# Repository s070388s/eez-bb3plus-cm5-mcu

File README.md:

### This is a WORK IN PROGRESS!

---

### Ownership and License
The contributors are listed in CONTRIB.TXT. 

### Overview

The MCU module uses a high performance STM32 MCU and is pin compatible with Raspberry Pi CM5. The MCU cannot generate an HDMI compatible signal, so a TI TFP410 is used to convert 24-bit RGB to HDMI compatible signal. Since the BB3+ offers dual display: a built-in 5" TFT touchscreen and an external monitor, a 1:2 high speed mux (TS3DV642) is used for destination selection.

### Feature list

* [Raspberry Pi CM5](https://www.raspberrypi.com/products/compute-module-5) form factor (55 x 45 mm)
* [STM32H7R7L8H6H](https://www.st.com/en/microcontrollers-microprocessors/stm32h7r7l8.html) 32-bit High-Performance Arm Cortex-M7 MCU, 600 MHz, NeoChrom GPU
* 32 MB PSRAM
* 32 MB Flash memory
* 4 GB eMMC (100-pin FBGA)
* Two USB ports (1x FS with 1:2 Mux , 1x FS/HS)
* 10/100 Mbps Ethernet
* 24-bit color video output with 1:2 MUX (HDMI® compatible)
* 6-layer PCB (without buried/blind vias)

### Related topics and links

* Intergalaktik [BB3-CM4](https://intergalaktik.eu/projects/bb3-cm4)
* [EEZ BB3+](https://github.com/eez-open/eez-bb3plus)
* [DIB DCP405+](https://github.com/eez-open/dib-dcp405plus) power module
* [EEZ BB3](https://github.com/eez-open/modular-psu)
* [EEZ Studio](https://www.envox.eu/studio/studio-introduction)
* [Discord](https://discord.com/invite/q5KAeeenNG) server
* [X](https://x.com/envox) (ex Twitter)
* [YouTube](https://www.youtube.com/c/eezopen) channel
* [EEVblog forum](https://www.eevblog.com/forum/projects/eez-h25005-a-possible-successor-of-eez-h24005-programmable-power-supply/) discussion

---

This work is financed by [NLnet](https://nlnet.nl/project/BB3-CM5/) foundation

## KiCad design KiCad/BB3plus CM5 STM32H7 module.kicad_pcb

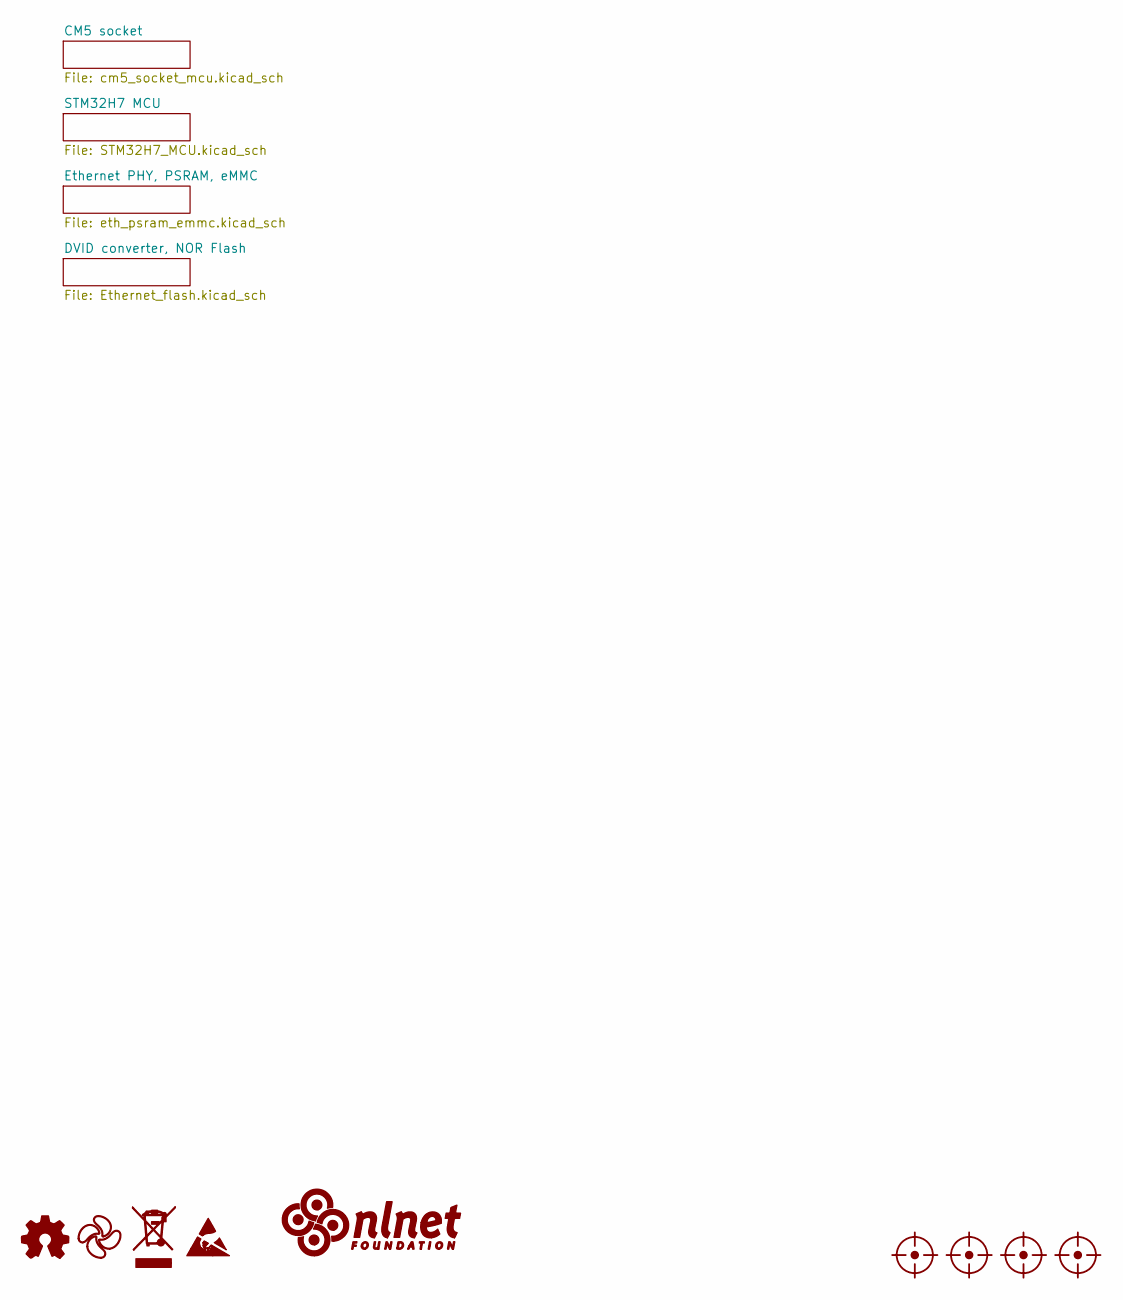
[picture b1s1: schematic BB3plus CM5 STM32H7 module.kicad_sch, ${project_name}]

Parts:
FM1, FM2, FM3, FM4: Fiducial_0.75mm_Mask1.5mm
LOGO1: Open HW logo
LOGO2: EEZ logo; EEZ logo (outline 6mm)
LOGO3: WEEE logo
LOGO4: ESD logo
LOGO5: NLnet logo

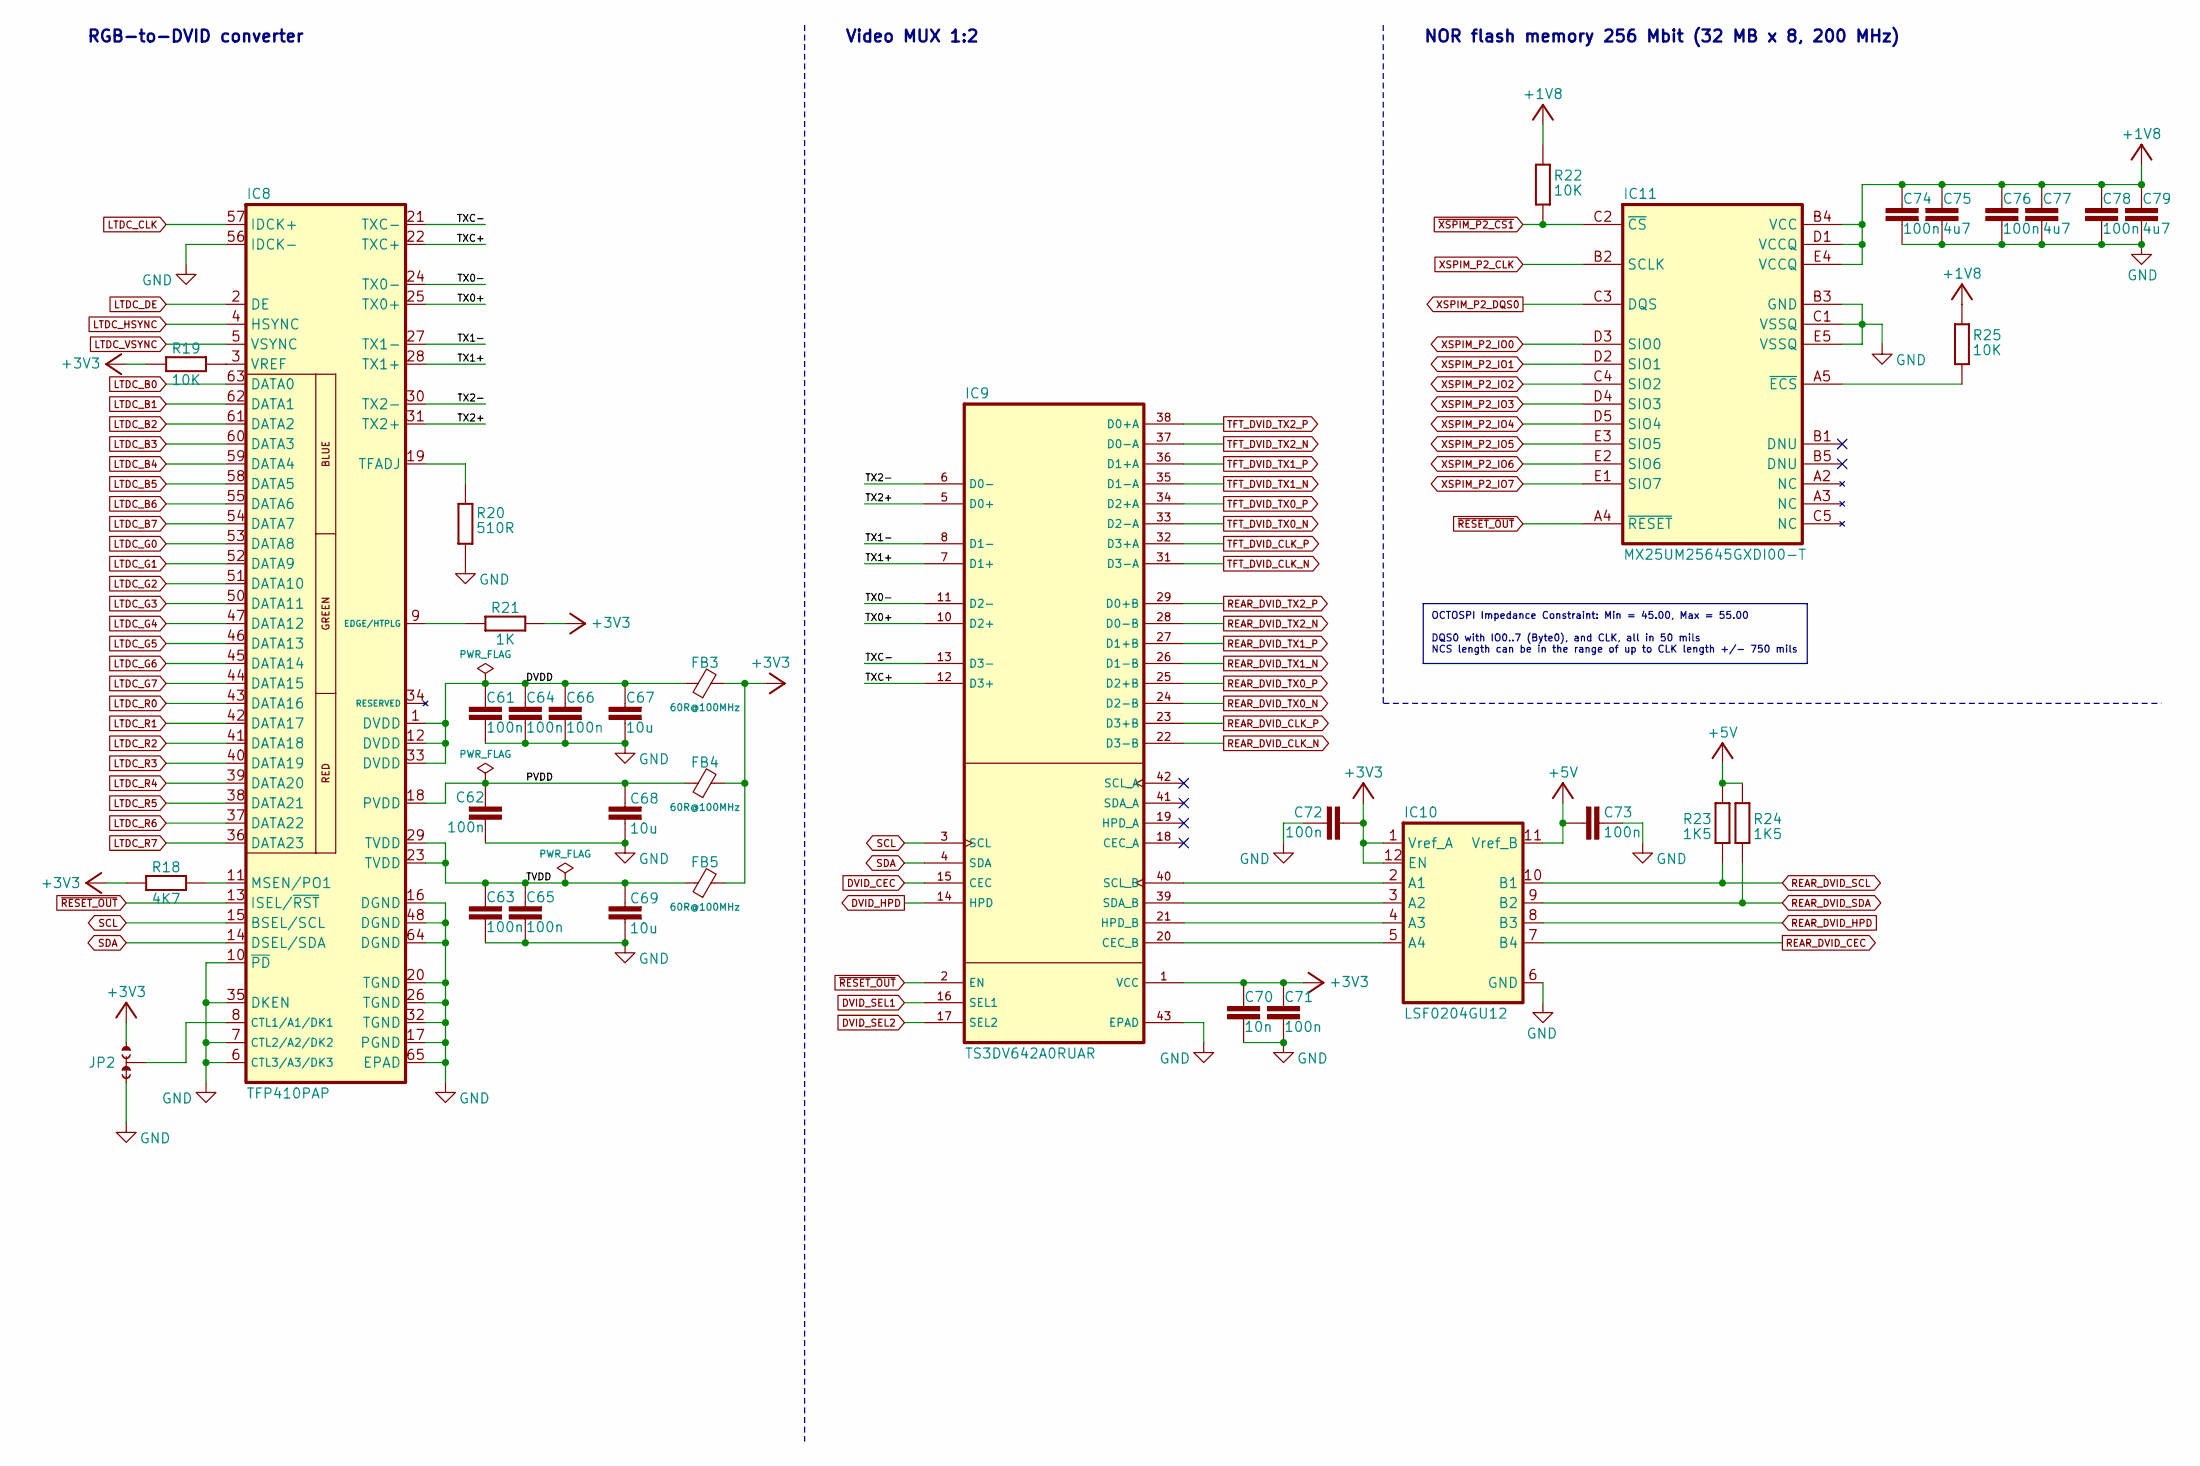
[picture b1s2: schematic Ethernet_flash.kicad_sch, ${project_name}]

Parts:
C61, C62, C63, C64, C65, C66, C71, C72, C73, C74, C76, C78: 100n; C_0402_1005Metric; DigiKey 490-6287-1-ND
C67, C68, C69: 10u; C_0603_1608Metric; DigiKey 1276-1052-6-ND
C70: 10n; C_0402_1005Metric; DigiKey 490-6309-1-ND
C75, C77, C79: 4u7; C_0603_1608Metric; DigiKey 1276-1044-1-ND
FB3, FB4, FB5: 60R@100MHz; BEAD0603; DigiKey 490-7809-1-ND
IC8: TFP410PAP; PAP64_5X5-L; DigiKey 296-12666-ND
IC9: TS3DV642A0RUAR; RUA42_7P55X2P05; DigiKey 296-39510-1-ND
IC10: LSF0204GU12; XQFN12_SOT1174-1_NEX-L; DigiKey 1727-LSF0102DCHCT-ND
IC11: MX25UM25645GXDI00-T; APS256XXN-OBR-BG_APY-L; DigiKey 1092-MX25UM25645GXDI00-ND
JP2: JP3 shorted (0603)
R18: 4K7; R_0402_1005Metric; DigiKey 13-RC0402FR-104K7LCT-ND
R19, R22, R25: 10K; R_0402_1005Metric; DigiKey 311-10.0KLRCT-ND
R20: 510R; R_0402_1005Metric; DigiKey 13-RC0402FR-13510RLCT-ND
R21: 1K; R_0402_1005Metric; DigiKey 13-RC0402FR-131KLCT-ND
R23, R24: 1K5; R_0402_1005Metric; DigiKey 311-1.50KLRCT-ND

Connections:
+1V8: C74.1, C75.1, C76.1, C77.1, C78.1, C79.1, IC11.B4 (VCC), IC11.D1 (VCCQ), IC11.E4 (VCCQ), R22.2, R25.2; also elsewhere on the board
+3V3: C70.1, C71.1, C72.2, FB3.2, FB4.2, FB5.2, IC9.1 (VCC), IC10.1 (Vref_A), IC10.12 (EN), JP2.NO, R18.1, R19.2, R21.2; also elsewhere on the board
+5V: C73.2, IC10.11 (Vref_B), R23.2, R24.2; also elsewhere on the board
/DVID converter, NOR Flash/DVDD: C61.1, C64.1, C66.1, C67.1, FB3.1, IC8.1 (DVDD), IC8.12 (DVDD), IC8.33 (DVDD)
/DVID converter, NOR Flash/PVDD: C62.1, C68.2, FB4.1, IC8.18 (PVDD)
/DVID converter, NOR Flash/TVDD: C63.1, C65.1, C69.2, FB5.1, IC8.23 (TVDD), IC8.29 (TVDD)
/DVID converter, NOR Flash/TX0+: IC8.25 (TX0+), IC9.10 (D2+)
/DVID converter, NOR Flash/TX0-: IC8.24 (TX0-), IC9.11 (D2-)
/DVID converter, NOR Flash/TX1+: IC8.28 (TX1+), IC9.7 (D1+)
/DVID converter, NOR Flash/TX1-: IC8.27 (TX1-), IC9.8 (D1-)
/DVID converter, NOR Flash/TX2+: IC8.31 (TX2+), IC9.5 (D0+)
/DVID converter, NOR Flash/TX2-: IC8.30 (TX2-), IC9.6 (D0-)
/DVID converter, NOR Flash/TXC+: IC8.22 (TXC+), IC9.12 (D3+)
/DVID converter, NOR Flash/TXC-: IC8.21 (TXC-), IC9.13 (D3-)
DVID_CEC: IC9.15 (CEC); also elsewhere on the board
DVID_HPD: IC9.14 (HPD); also elsewhere on the board
DVID_SEL1: IC9.16 (SEL1); also elsewhere on the board
DVID_SEL2: IC9.17 (SEL2); also elsewhere on the board
GND: C61.2, C62.2, C63.2, C64.2, C65.2, C66.2, C67.2, C68.1, C69.1, C70.2, C71.2, C72.1, C73.1, C74.2, C75.2, C76.2, C77.2, C78.2, C79.2, IC8.6 (CTL3/A3/DK3), IC8.7 (CTL2/A2/DK2), IC8.10 (~PD), IC8.16 (DGND), IC8.17 (PGND), IC8.20 (TGND), IC8.26 (TGND), IC8.32 (TGND), IC8.35 (DKEN), IC8.48 (DGND), IC8.56 (IDCK-), IC8.64 (DGND), IC8.65 (EPAD), IC9.43 (EPAD), IC10.6 (GND), IC11.B3 (GND), IC11.C1 (VSSQ), IC11.E5 (VSSQ), JP2.NC, R20.2; also elsewhere on the board
LTDC_B0: IC8.63 (DATA0); also elsewhere on the board
LTDC_B1: IC8.62 (DATA1); also elsewhere on the board
LTDC_B2: IC8.61 (DATA2); also elsewhere on the board
LTDC_B3: IC8.60 (DATA3); also elsewhere on the board
LTDC_B4: IC8.59 (DATA4); also elsewhere on the board
LTDC_B5: IC8.58 (DATA5); also elsewhere on the board
LTDC_B6: IC8.55 (DATA6); also elsewhere on the board
LTDC_B7: IC8.54 (DATA7); also elsewhere on the board
LTDC_CLK: IC8.57 (IDCK+); also elsewhere on the board
LTDC_DE: IC8.2 (DE); also elsewhere on the board
LTDC_G0: IC8.53 (DATA8); also elsewhere on the board
LTDC_G1: IC8.52 (DATA9); also elsewhere on the board
LTDC_G2: IC8.51 (DATA10); also elsewhere on the board
LTDC_G3: IC8.50 (DATA11); also elsewhere on the board
LTDC_G4: IC8.47 (DATA12); also elsewhere on the board
LTDC_G5: IC8.46 (DATA13); also elsewhere on the board
LTDC_G6: IC8.45 (DATA14); also elsewhere on the board
LTDC_G7: IC8.44 (DATA15); also elsewhere on the board
LTDC_HSYNC: IC8.4 (HSYNC); also elsewhere on the board
LTDC_R0: IC8.43 (DATA16); also elsewhere on the board
LTDC_R1: IC8.42 (DATA17); also elsewhere on the board
LTDC_R2: IC8.41 (DATA18); also elsewhere on the board
LTDC_R3: IC8.40 (DATA19); also elsewhere on the board
LTDC_R4: IC8.39 (DATA20); also elsewhere on the board
LTDC_R5: IC8.38 (DATA21); also elsewhere on the board
LTDC_R6: IC8.37 (DATA22); also elsewhere on the board
LTDC_R7: IC8.36 (DATA23); also elsewhere on the board
LTDC_VSYNC: IC8.5 (VSYNC); also elsewhere on the board
unnamed: IC8.8 (CTL1/A1/DK1), JP2.COM
unnamed: IC8.9 (EDGE/HTPLG), R21.1
unnamed: IC8.11 (MSEN/PO1), R18.2
unnamed: IC8.19 (TFADJ), R20.1
unnamed: IC8.3 (VREF), R19.1
unnamed: IC9.40 (SCL_B), IC10.2 (A1)
unnamed: IC9.39 (SDA_B), IC10.3 (A2)
unnamed: IC9.21 (HPD_B), IC10.4 (A3)
unnamed: IC9.20 (CEC_B), IC10.5 (A4)
unnamed: IC11.A5 (~ECS), R25.1
REAR_DVID_CEC: IC10.7 (B4); also elsewhere on the board
REAR_DVID_CLK_N: IC9.22 (D3-B); also elsewhere on the board
REAR_DVID_CLK_P: IC9.23 (D3+B); also elsewhere on the board
REAR_DVID_HPD: IC10.8 (B3); also elsewhere on the board
REAR_DVID_SCL: IC10.10 (B1), R23.1; also elsewhere on the board
REAR_DVID_SDA: IC10.9 (B2), R24.1; also elsewhere on the board
REAR_DVID_TX0_N: IC9.24 (D2-B); also elsewhere on the board
REAR_DVID_TX0_P: IC9.25 (D2+B); also elsewhere on the board
REAR_DVID_TX1_N: IC9.26 (D1-B); also elsewhere on the board
REAR_DVID_TX1_P: IC9.27 (D1+B); also elsewhere on the board
REAR_DVID_TX2_N: IC9.28 (D0-B); also elsewhere on the board
REAR_DVID_TX2_P: IC9.29 (D0+B); also elsewhere on the board
SCL: IC8.15 (BSEL/SCL), IC9.3 (SCL); also elsewhere on the board
SDA: IC8.14 (DSEL/SDA), IC9.4 (SDA); also elsewhere on the board
TFT_DVID_CLK_N: IC9.31 (D3-A); also elsewhere on the board
TFT_DVID_CLK_P: IC9.32 (D3+A); also elsewhere on the board
TFT_DVID_TX0_N: IC9.33 (D2-A); also elsewhere on the board
TFT_DVID_TX0_P: IC9.34 (D2+A); also elsewhere on the board
TFT_DVID_TX1_N: IC9.35 (D1-A); also elsewhere on the board
TFT_DVID_TX1_P: IC9.36 (D1+A); also elsewhere on the board
TFT_DVID_TX2_N: IC9.37 (D0-A); also elsewhere on the board
TFT_DVID_TX2_P: IC9.38 (D0+A); also elsewhere on the board
XSPIM_P2_CLK: IC11.B2 (SCLK); also elsewhere on the board
XSPIM_P2_DQS0: IC11.C3 (DQS); also elsewhere on the board
XSPIM_P2_IO0: IC11.D3 (SIO0); also elsewhere on the board
XSPIM_P2_IO1: IC11.D2 (SIO1); also elsewhere on the board
XSPIM_P2_IO2: IC11.C4 (SIO2); also elsewhere on the board
XSPIM_P2_IO3: IC11.D4 (SIO3); also elsewhere on the board
XSPIM_P2_IO4: IC11.D5 (SIO4); also elsewhere on the board
XSPIM_P2_IO5: IC11.E3 (SIO5); also elsewhere on the board
XSPIM_P2_IO6: IC11.E2 (SIO6); also elsewhere on the board
XSPIM_P2_IO7: IC11.E1 (SIO7); also elsewhere on the board
~RESET_OUT: IC8.13 (ISEL/~RST), IC9.2 (EN), IC11.A4 (~RESET); also elsewhere on the board
~XSPIM_P2_CS1: IC11.C2 (~CS), R22.1; also elsewhere on the board

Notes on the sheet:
RGB-to-DVID converter
Video MUX 1:2
NOR flash memory 256 Mbit (32 MB x 8, 200 MHz)
OCTOSPI Impedance Constraint: Min = 45.00, Max = 55.00 DQS0 with IO0..7 (Byte0), and CLK, all in 50 mils NCS length can be in the range of up to CLK length +/- 750 mils

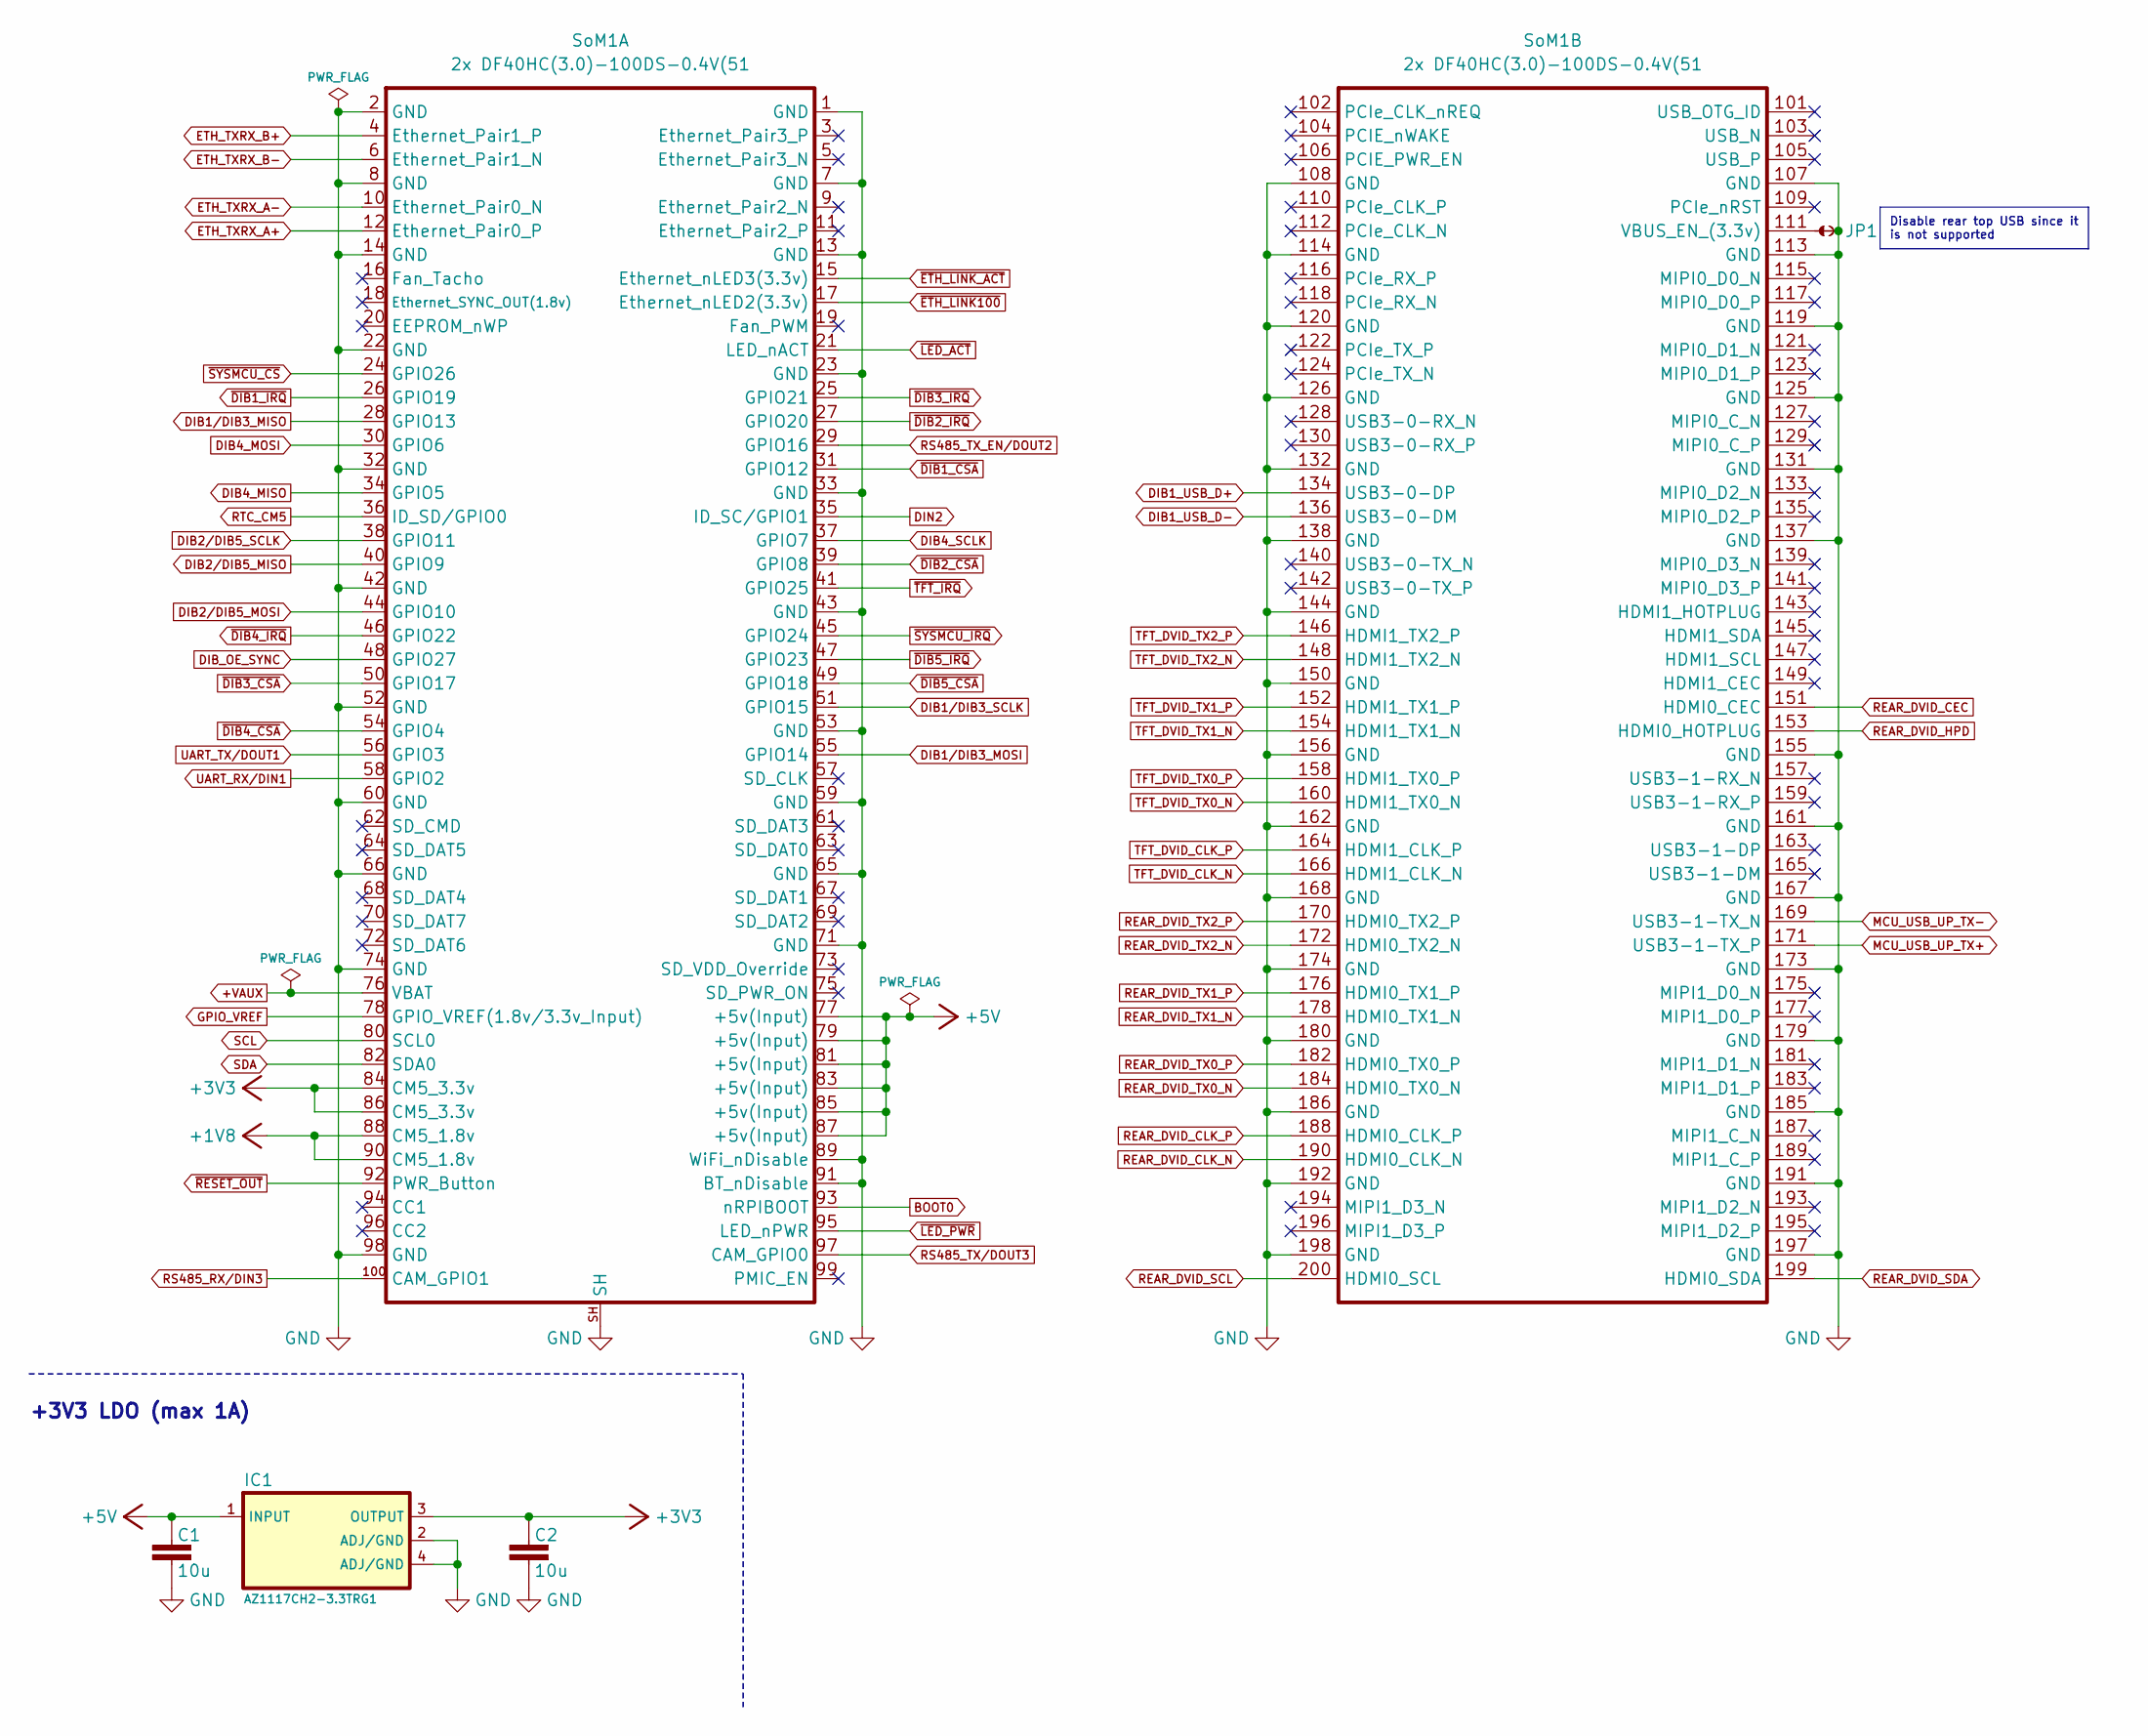
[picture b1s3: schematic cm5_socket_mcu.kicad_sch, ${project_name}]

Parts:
C1, C2: 10u; C_0603_1608Metric; DigiKey 1276-1052-6-ND
IC1: AZ1117CH2-3.3TRG1; SOT223; DigiKey 31-AZ1117CH2-3.3TRG1CT-ND
JP1: JP2 shorted (0603)
SoM1: 2x DF40HC(3.0)-100DS-0.4V(51; Raspberry-Pi-CM5 (SoM); DigiKey H11614CT-ND

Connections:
+1V8: SoM1.88 (CM5_1.8v), SoM1.90 (CM5_1.8v); also elsewhere on the board
+3V3: C2.2, IC1.3 (OUTPUT), SoM1.84 (CM5_3.3v), SoM1.86 (CM5_3.3v); also elsewhere on the board
+5V: C1.2, IC1.1 (INPUT), SoM1.77 (+5v(Input)), SoM1.79 (+5v(Input)), SoM1.81 (+5v(Input)), SoM1.83 (+5v(Input)), SoM1.85 (+5v(Input)), SoM1.87 (+5v(Input)); also elsewhere on the board
+VAUX: SoM1.76 (VBAT); also elsewhere on the board
BOOT0: SoM1.93 (nRPIBOOT); also elsewhere on the board
DIB1_USB_D+: SoM1.134 (USB3-0-DP); also elsewhere on the board
DIB1_USB_D-: SoM1.136 (USB3-0-DM); also elsewhere on the board
DIB1/DIB3_MISO: SoM1.28 (GPIO13); also elsewhere on the board
DIB1/DIB3_MOSI: SoM1.55 (GPIO14); also elsewhere on the board
DIB1/DIB3_SCLK: SoM1.51 (GPIO15); also elsewhere on the board
DIB2/DIB5_MISO: SoM1.40 (GPIO9); also elsewhere on the board
DIB2/DIB5_MOSI: SoM1.44 (GPIO10); also elsewhere on the board
DIB2/DIB5_SCLK: SoM1.38 (GPIO11); also elsewhere on the board
DIB4_MISO: SoM1.34 (GPIO5); also elsewhere on the board
DIB4_MOSI: SoM1.30 (GPIO6); also elsewhere on the board
DIB4_SCLK: SoM1.37 (GPIO7); also elsewhere on the board
DIB_OE_SYNC: SoM1.48 (GPIO27); also elsewhere on the board
DIN2: SoM1.35 (ID_SC/GPIO1); also elsewhere on the board
ETH_TXRX_A+: SoM1.12 (Ethernet_Pair0_P); also elsewhere on the board
ETH_TXRX_A-: SoM1.10 (Ethernet_Pair0_N); also elsewhere on the board
ETH_TXRX_B+: SoM1.4 (Ethernet_Pair1_P); also elsewhere on the board
ETH_TXRX_B-: SoM1.6 (Ethernet_Pair1_N); also elsewhere on the board
GND: C1.1, C2.1, IC1.2 (ADJ/GND), IC1.4 (ADJ/GND), JP1.2, SoM1.1 (GND), SoM1.2 (GND), SoM1.7 (GND), SoM1.8 (GND), SoM1.13 (GND), SoM1.14 (GND), SoM1.22 (GND), SoM1.23 (GND), SoM1.32 (GND), SoM1.33 (GND), SoM1.42 (GND), SoM1.43 (GND), SoM1.52 (GND), SoM1.53 (GND), SoM1.59 (GND), SoM1.60 (GND), SoM1.65 (GND), SoM1.66 (GND), SoM1.71 (GND), SoM1.74 (GND), SoM1.89 (WiFi_nDisable), SoM1.91 (BT_nDisable), SoM1.98 (GND), SoM1.107 (GND), SoM1.108 (GND), SoM1.113 (GND), SoM1.114 (GND), SoM1.119 (GND), SoM1.120 (GND), SoM1.125 (GND), SoM1.126 (GND), SoM1.131 (GND), SoM1.132 (GND), SoM1.137 (GND), SoM1.138 (GND), SoM1.144 (GND), SoM1.150 (GND), SoM1.155 (GND), SoM1.156 (GND), SoM1.161 (GND), SoM1.162 (GND), SoM1.167 (GND), SoM1.168 (GND), SoM1.173 (GND), SoM1.174 (GND), SoM1.179 (GND), SoM1.180 (GND), SoM1.185 (GND), SoM1.186 (GND), SoM1.191 (GND), SoM1.192 (GND), SoM1.197 (GND), SoM1.198 (GND), SoM1.SH; also elsewhere on the board
GPIO_VREF: SoM1.78 (GPIO_VREF(1.8v/3.3v_Input)); also elsewhere on the board
MCU_USB_UP_TX+: SoM1.171 (USB3-1-TX_P); also elsewhere on the board
MCU_USB_UP_TX-: SoM1.169 (USB3-1-TX_N); also elsewhere on the board
unnamed: JP1.1, SoM1.111 (VBUS_EN_(3.3v))
REAR_DVID_CEC: SoM1.151 (HDMI0_CEC); also elsewhere on the board
REAR_DVID_CLK_N: SoM1.190 (HDMI0_CLK_N); also elsewhere on the board
REAR_DVID_CLK_P: SoM1.188 (HDMI0_CLK_P); also elsewhere on the board
REAR_DVID_HPD: SoM1.153 (HDMI0_HOTPLUG); also elsewhere on the board
REAR_DVID_SCL: SoM1.200 (HDMI0_SCL); also elsewhere on the board
REAR_DVID_SDA: SoM1.199 (HDMI0_SDA); also elsewhere on the board
REAR_DVID_TX0_N: SoM1.184 (HDMI0_TX0_N); also elsewhere on the board
REAR_DVID_TX0_P: SoM1.182 (HDMI0_TX0_P); also elsewhere on the board
REAR_DVID_TX1_N: SoM1.178 (HDMI0_TX1_N); also elsewhere on the board
REAR_DVID_TX1_P: SoM1.176 (HDMI0_TX1_P); also elsewhere on the board
REAR_DVID_TX2_N: SoM1.172 (HDMI0_TX2_N); also elsewhere on the board
REAR_DVID_TX2_P: SoM1.170 (HDMI0_TX2_P); also elsewhere on the board
RS485_RX/DIN3: SoM1.100 (CAM_GPIO1); also elsewhere on the board
RS485_TX_EN/DOUT2: SoM1.29 (GPIO16); also elsewhere on the board
RS485_TX/DOUT3: SoM1.97 (CAM_GPIO0); also elsewhere on the board
RTC_CM5: SoM1.36 (ID_SD/GPIO0); also elsewhere on the board
SCL: SoM1.80 (SCL0); also elsewhere on the board
SDA: SoM1.82 (SDA0); also elsewhere on the board
TFT_DVID_CLK_N: SoM1.166 (HDMI1_CLK_N); also elsewhere on the board
TFT_DVID_CLK_P: SoM1.164 (HDMI1_CLK_P); also elsewhere on the board
TFT_DVID_TX0_N: SoM1.160 (HDMI1_TX0_N); also elsewhere on the board
TFT_DVID_TX0_P: SoM1.158 (HDMI1_TX0_P); also elsewhere on the board
TFT_DVID_TX1_N: SoM1.154 (HDMI1_TX1_N); also elsewhere on the board
TFT_DVID_TX1_P: SoM1.152 (HDMI1_TX1_P); also elsewhere on the board
TFT_DVID_TX2_N: SoM1.148 (HDMI1_TX2_N); also elsewhere on the board
TFT_DVID_TX2_P: SoM1.146 (HDMI1_TX2_P); also elsewhere on the board
UART_RX/DIN1: SoM1.58 (GPIO2); also elsewhere on the board
UART_TX/DOUT1: SoM1.56 (GPIO3); also elsewhere on the board
~DIB1_CSA: SoM1.31 (GPIO12); also elsewhere on the board
~DIB1_IRQ: SoM1.26 (GPIO19); also elsewhere on the board
~DIB2_CSA: SoM1.39 (GPIO8); also elsewhere on the board
~DIB2_IRQ: SoM1.27 (GPIO20); also elsewhere on the board
~DIB3_CSA: SoM1.50 (GPIO17); also elsewhere on the board
~DIB3_IRQ: SoM1.25 (GPIO21); also elsewhere on the board
~DIB4_CSA: SoM1.54 (GPIO4); also elsewhere on the board
~DIB4_IRQ: SoM1.46 (GPIO22); also elsewhere on the board
~DIB5_CSA: SoM1.49 (GPIO18); also elsewhere on the board
~DIB5_IRQ: SoM1.47 (GPIO23); also elsewhere on the board
~ETH_LINK100: SoM1.17 (Ethernet_nLED2(3.3v)); also elsewhere on the board
~ETH_LINK_ACT: SoM1.15 (Ethernet_nLED3(3.3v)); also elsewhere on the board
~LED_ACT: SoM1.21 (LED_nACT); also elsewhere on the board
~LED_PWR: SoM1.95 (LED_nPWR); also elsewhere on the board
~RESET_OUT: SoM1.92 (PWR_Button); also elsewhere on the board
~SYSMCU_CS: SoM1.24 (GPIO26); also elsewhere on the board
~SYSMCU_IRQ: SoM1.45 (GPIO24); also elsewhere on the board
~TFT_IRQ: SoM1.41 (GPIO25); also elsewhere on the board

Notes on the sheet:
+3V3 LDO (max 1A)
Disable rear top USB since it is not supported

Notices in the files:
parts and their libraries:
project_license: Licensed under the TAPR Open Hardware License (www.tapr.org/OHL)
